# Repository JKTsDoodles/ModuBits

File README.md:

# ModuBits
This is a versatile set of prototyping boards and modules designed to fit chassis measuring 100mm wide and 120mm deep. Each module allows for easy integration of various connectors and components, enabling efficient prototyping and experimentation in electronics projects. 

ECAD tool: KiCad 9.99 (nightly)

MCAD tool: FreeCAD 1.0.2

Compatible chassis:
- [K93-10436-H7-L120](https://jlcmc.com/product/b/U01/BR9212/aluminum-box-(jlc)---104*36*120mm,-split,-monolithic)
- [K97-10473-H7-L120](https://jlcmc.com/product/b/U01/BR9241/aluminum-box-(jlc)---104*73*120mm,-split,-monolithic)
- [K96-10463-H7-L120](https://jlcmc.com/product/b/U01/BR9259/aluminum-box-(jlc)---104*63*120mm,-split,-monolithic)
- [K127-13031-H7-L120](https://jlcmc.com/product/b/U01/BR10337/aluminum-box-(jlc)---130*31*120mm,-monolithic,-with-handles)

BNC module:

Note that BNC connector parts of this type may share the same footprint but differ in the height of the connector in order to vendor lock their customers. Check for the height of your part, which is 6.25mm in this example.

BNC reference design:
  
Chassis K127-13031-H7-L120:
  
Chassis K93-10436-H7-L120:
  
Chassis K97-10473-H7-L120:
  
Chassis K96-10463-H7-L120:

Barrel Jack module (PJ-063AH):

Barrel jack reference design:
  
Chassis K127-13031-H7-L120:
  
Chassis K93-10436-H7-L120:
  
Chassis K97-10473-H7-L120:
  
Chassis K96-10463-H7-L120:

3.5mm Audio Jack module (SJ3-35083D-TR):

Audio jack reference design:

Chassis K127-13031-H7-L120:
  
Chassis K93-10436-H7-L120:
  
Chassis K97-10473-H7-L120:
  
Chassis K96-10463-H7-L120:

4mm Banana Jack module (Banana_Cliff_FCR7350B_S16N-PC_Horizontal):

4mm Banana jack reference design:
  
Chassis K127-13031-H7-L120:
  
Chassis K93-10436-H7-L120:
  
Chassis K97-10473-H7-L120:
  
Chassis K96-10463-H7-L120:

Connectorless PMMA plastic optic fiber receiver (IF-D91B):

Connectorless PMMA plastic optic fiber receiver reference design:

Chassis K127-13031-H7-L120:
  
Chassis K93-10436-H7-L120:
  
Chassis K97-10473-H7-L120:
  
Chassis K96-10463-H7-L120:

Connectorless PMMA plastic optic fiber transmitter (IF-E96E):

Connectorless PMMA plastic optic fiber transmitter reference design:

Chassis K127-13031-H7-L120:
  
Chassis K93-10436-H7-L120:
  
Chassis K97-10473-H7-L120:
  
Chassis K96-10463-H7-L120:

Right-angle tactile switch (PTS645V):

Right-angle tactile switch reference design:

Chassis K127-13031-H7-L120:
  
Chassis K93-10436-H7-L120:
  
Chassis K97-10473-H7-L120:
  
Chassis K96-10463-H7-L120:

The indices of the modules used to determine the position of the modules on the protoboard:
<p align="center">

</p>

The white bars at the bottom edge of the protoboard mark the decadal numbers and the index has a range of 0..72.

The following table lists the reference coordinates for the frontpanel hole if the module is sitting on the reference point (index == 0). The coordinates of the respective frontpanel hole can be calculated by adding (if the protoboard is component side up) or subtracting (if the protoboard is component side down) 1.27mm times index (of the module), since the modules are on a 50mil(1.27mm) grid.

I may write a FreeCAD script at some point to automate the generation of the frontpanel MCAD files.

| Chassis                         | Cutout Coordinates [X/Y] mm 4mm Banana D=11.5mm | Cutout Coordinates [X/Y] mm BNC D=13mm | Cutout Coordinates [X/Y] mm IF-D91B D=6.3mm | Cutout Coordinates [X/Y] mm IF-E96E D=6.3mm | Cutout Coordinates [X/Y] mm PJ-063AH D=7mm | Cutout Coordinates [X/Y] mm PTS645V D=3.6mm | Cutout Coordinates [X/Y] mm SJ3-35083D-TR D=5.2mm |
|---------------------------------|-------------------------------------------------|----------------------------------------|---------------------------------------------|---------------------------------------------|--------------------------------------------|---------------------------------------------|---------------------------------------------------|
| K93-10436-H7-L120, level1, up   | 12.63+index*1.27 / 19.92                        | 15.18+index*1.27 / 20.72               | 11.36+index*1.27 / 20.6                     | 11.36+index*1.27 / 20.6                     | 12.63+index*1.27 / 18.62                   | 11.38+index*1.27 / 17.12                    | 10.09+index*1.27 / 16.15                          |
| K127-13031-H7-L120, level1, up  | 13.03+index*1.27 / 18.33                        | 15.55+index*1.27 / 19.14               | 11.76+index*1.27 / 19.02                    | 11.76+index*1.27 / 19.02                    | 13.03+index*1.27 / 17.02                   | 11.79+index*1.27 / 15.53                    | 10.49+index*1.27 / 14.56                          |
| K97-10473-H7-L120, level1, up   | 12.63+index*1.27 / 19.92                        | 15.17+index*1.27 / 20.70               | 11.36+index*1.27 / 20.64                    | 11.36+index*1.27 / 20.64                    | 12.63+index*1.27 / 18.62                   | 11.38+index*1.27 / 17.12                    | 10.09+index*1.27 / 16.15                          |
| K97-10473-H7-L120, level4, down | 91.37-index*1.27 / 53.06                        | 88.83-index*1.27 / 52.25               | 92.64-index*1.27 / 52.41                    | 92.64-index*1.27 / 52.41                    | 91.37-index*1.27 / 54.36                   | 92.62-index*1.27 / 55.86                    | 93.91-index*1.27 / 56.83                          |
| K96-10463-H7-L120, level1, up   | 12.63+index*1.27 / 19.93                        | 15.17+index*1.27 / 20.74               | 11.36+index*1.27 / 20.58                    | 11.36+index*1.27 / 20.58                    | 12.63+index*1.27 / 18.63                   | 11.38+index*1.27 / 17.14                    | 10.09+index*1.27 / 16.16                          |
| K96-10463-H7-L120, level4, down | 91.37-index*1.27 / 43.07                        | 88.83-index*1.27 / 42.26               | 92.64-index*1.27 / 42.35                    | 92.64-index*1.27 / 42.35                    | 91.37-index*1.27 / 44.38                   | 92.62-index*1.27 / 45.88                    | 93.91-index*1.27 / 46.84                          |

Following frontpanel was generated by opening "K93-10436-H7-L120_frontpanel_blank.FCStd" and plopping the python script "config_panel_K93-10436.py" into the Python console of FreeCAD. This script is hard-coded and ugly, yes, I'm acutely aware but it's also easy to read / understand and I'm not a coder. :3

The following image depicts the user area of the generator script that configures the frontpanel modifications.

I don't like my connectors getting mangled or smushed, so I designed a simple sacrificial part that will absorb the brunt of the impact force when the chassis is dropped or inadequately packaged. The part is attached to the chassis by using the M3 threads in the chassis, sandwiching the front panel between the chassis and the bumper part. I wanted to round the corners a bit further but I couldn't get the "fillet" tool to do its thing since the FreeCAD implementation is less forgiving than the equivalent tool in commercial MCAD tools.

The Tarantinorino is a corner piece with rubbery feet on all relevant sides to allow these chassis to either be used stacked like a tower or standing on the desk as an instrument centipede.

Same as above but with the improved DockLink-Frame:

This DockLink-Base-plate allows to secure stacks of chassis with a DockLink-Frame to any surface that can be screwed into with M6 bolts, like optical breadboards (M6, grid: 25mm):

Here's a short video showing off the DockLink-Base-plate with two attached chassis:
[DockLink-Base-plate](https://drive.proton.me/urls/AMNBBSNWWW#FV0qRknL7xtg)

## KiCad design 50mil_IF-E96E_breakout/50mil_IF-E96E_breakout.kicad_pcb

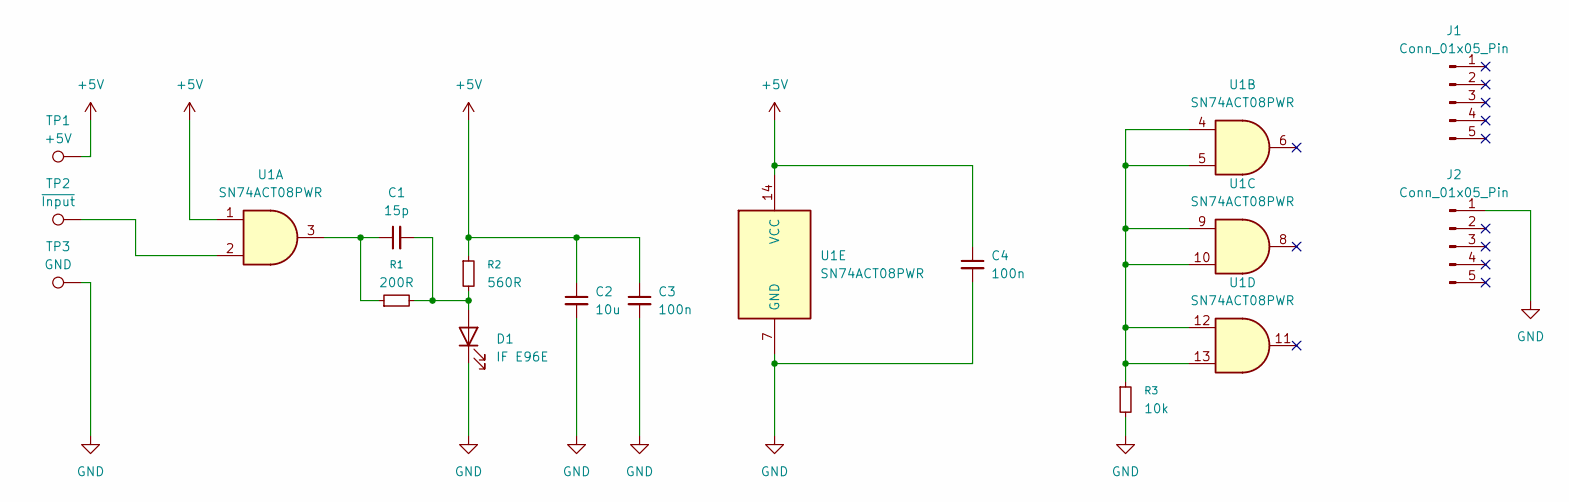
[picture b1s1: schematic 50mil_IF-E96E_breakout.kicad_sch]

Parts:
C1: 15p; C_0805_2012Metric_Pad1.18x1.45mm_HandSolder
C2: 10u; C_0805_2012Metric_Pad1.18x1.45mm_HandSolder
C3, C4: 100n; C_0805_2012Metric_Pad1.18x1.45mm_HandSolder
D1: IF E96E; IF-E96E
J1, J2: Conn_01x05_Pin; PinHeader_1x05_P1.27mm_Vertical
R1: 200R; R_0805_2012Metric_Pad1.20x1.40mm_HandSolder
R2: 560R; R_0805_2012Metric_Pad1.20x1.40mm_HandSolder
R3: 10k; R_0805_2012Metric_Pad1.20x1.40mm_HandSolder
TP1: +5V; TestPoint_THTPad_2.0x2.0mm_Drill1.0mm
TP2: ~{Input}; TestPoint_THTPad_2.0x2.0mm_Drill1.0mm
TP3: GND; TestPoint_THTPad_2.0x2.0mm_Drill1.0mm
U1: SN74ACT08PWR; TSSOP-14_4.4x5mm_P0.65mm

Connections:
+5V: C2.1, C3.1, C4.1, R2.1, TP1.1, U1.1, U1.14 (VCC)
GND: C2.2, C3.2, C4.2, D1.1 (K), J2.1, R3.2, TP3.1, U1.7 (GND)
unnamed: C1.1, R1.1, U1.3
unnamed: C1.2, D1.2 (A), R1.2, R2.2
unnamed: R3.1, U1.4, U1.5, U1.9, U1.10, U1.12, U1.13
unnamed: TP2.1, U1.2

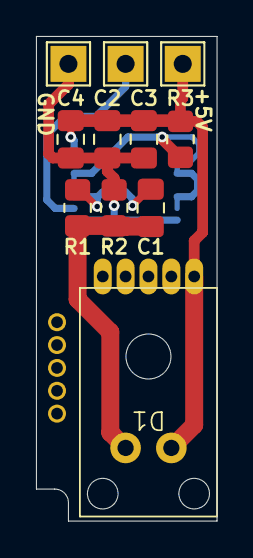
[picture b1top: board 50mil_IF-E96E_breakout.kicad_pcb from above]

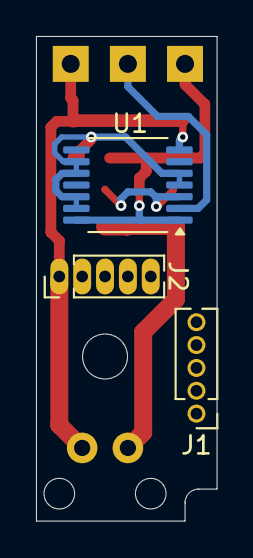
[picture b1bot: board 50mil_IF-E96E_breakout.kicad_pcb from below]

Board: 2 copper layers, 10.0 x 26.9 mm, 14 parts (3 on the bottom side), 6 nets.

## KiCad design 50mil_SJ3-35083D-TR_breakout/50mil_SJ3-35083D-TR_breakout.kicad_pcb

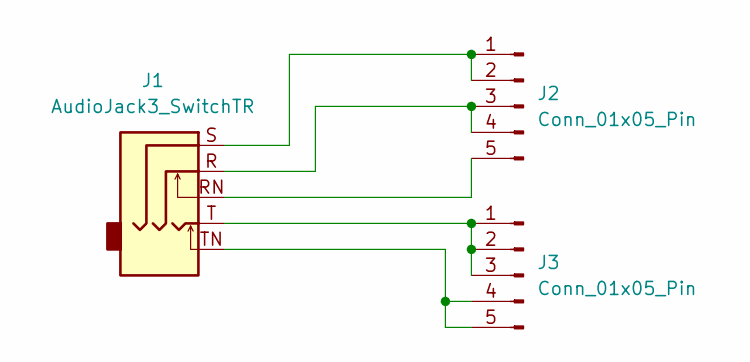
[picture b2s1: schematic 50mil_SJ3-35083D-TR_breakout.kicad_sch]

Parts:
J1: AudioJack3_SwitchTR; SJ3-35083D-TR
J2, J3: Conn_01x05_Pin; PinHeader_1x05_P1.27mm_Vertical

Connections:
unnamed: J1.S, J2.1, J2.2
unnamed: J1.R, J2.3, J2.4
unnamed: J1.RN, J2.5
unnamed: J1.T, J3.1, J3.2, J3.3
unnamed: J1.TN, J3.4, J3.5

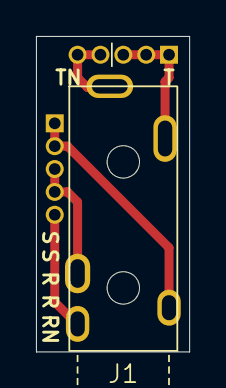
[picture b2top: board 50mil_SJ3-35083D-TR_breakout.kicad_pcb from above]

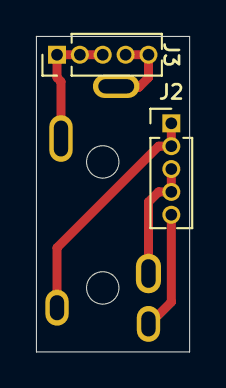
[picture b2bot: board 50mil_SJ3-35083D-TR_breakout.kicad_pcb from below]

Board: 2 copper layers, 8.5 x 17.5 mm, 3 parts (2 on the bottom side), 5 nets.

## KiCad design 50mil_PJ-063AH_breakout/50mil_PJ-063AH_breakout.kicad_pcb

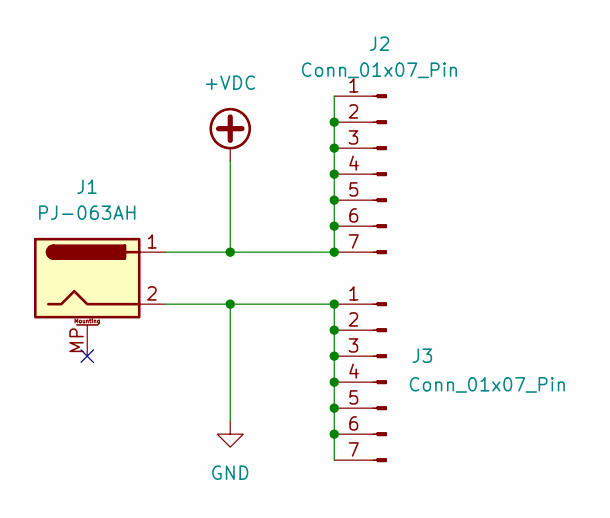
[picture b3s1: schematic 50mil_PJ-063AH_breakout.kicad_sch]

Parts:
J1: PJ-063AH; BarrelJack_CUI_PJ-063AH_Horizontal
J2, J3: Conn_01x07_Pin; PinHeader_1x07_P1.27mm_Vertical

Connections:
+VDC: J1.1, J2.1, J2.2, J2.3, J2.4, J2.5, J2.6, J2.7
GND: J1.2, J3.1, J3.2, J3.3, J3.4, J3.5, J3.6, J3.7

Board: 2 copper layers, 3 parts (2 on the bottom side), 2 nets, no tracks yet.

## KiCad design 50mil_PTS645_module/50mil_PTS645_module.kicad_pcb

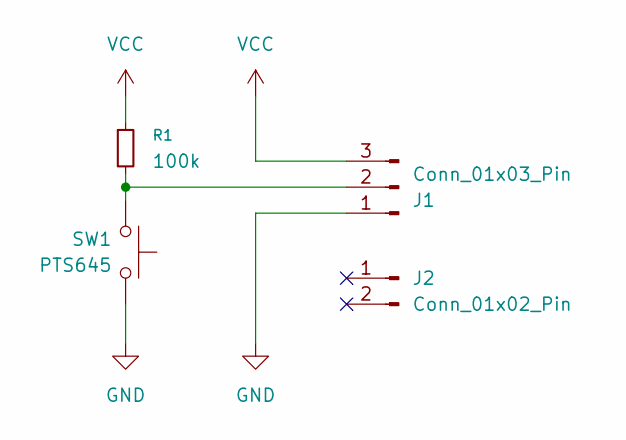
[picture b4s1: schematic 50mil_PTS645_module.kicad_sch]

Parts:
J1: Conn_01x03_Pin; PinHeader_1x03_P1.27mm_Vertical
J2: Conn_01x02_Pin; PinHeader_1x02_P1.27mm_Vertical
R1: 100k; R_0805_2012Metric_Pad1.20x1.40mm_HandSolder
SW1: PTS645; SW_Tactile_SPST_Angled_PTS645Vx58-2LFS

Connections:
GND: J1.1, SW1.1
unnamed: J1.2, R1.2, SW1.2
VCC: J1.3, R1.1

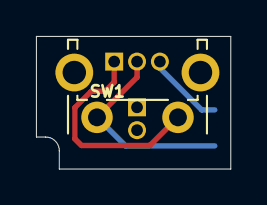
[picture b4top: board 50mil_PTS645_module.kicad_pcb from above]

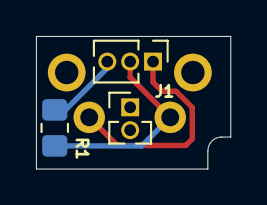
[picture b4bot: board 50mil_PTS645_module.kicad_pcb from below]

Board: 2 copper layers, 10.8 x 7.4 mm, 4 parts (3 on the bottom side), 3 nets.

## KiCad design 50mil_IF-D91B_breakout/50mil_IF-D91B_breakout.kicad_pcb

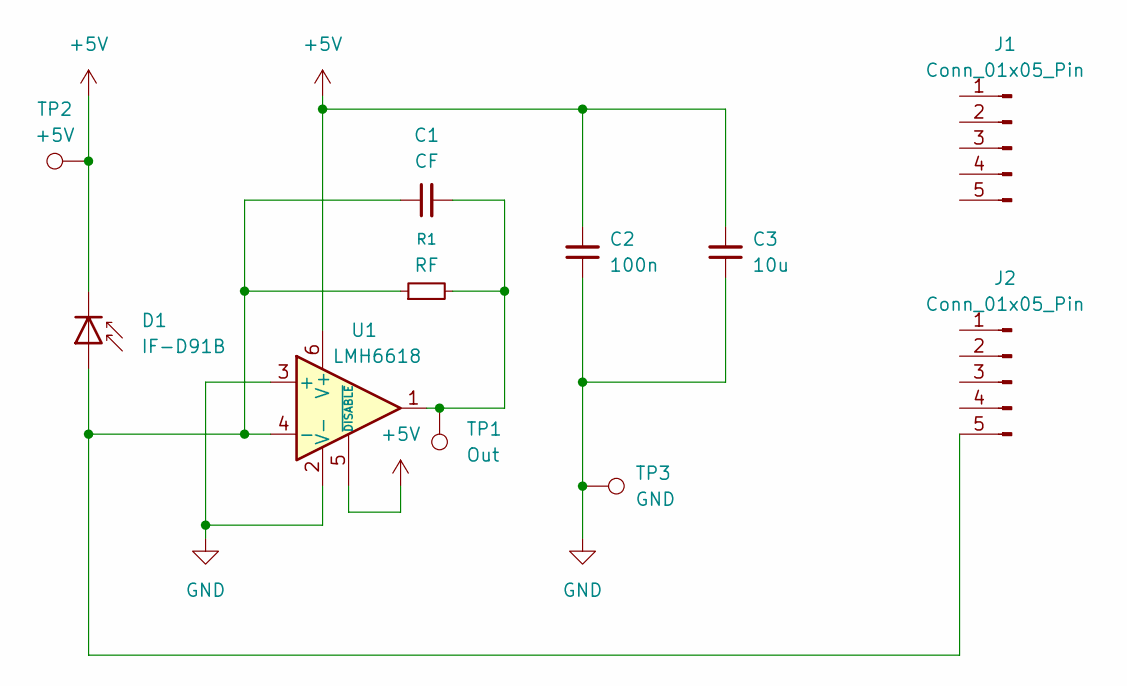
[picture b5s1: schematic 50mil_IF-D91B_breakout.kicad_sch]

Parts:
C1: CF; C_0805_2012Metric_Pad1.18x1.45mm_HandSolder
C2: 100n; C_0805_2012Metric_Pad1.18x1.45mm_HandSolder
C3: 10u; C_0805_2012Metric_Pad1.18x1.45mm_HandSolder
D1: IF-D91B
J1, J2: Conn_01x05_Pin; PinHeader_1x05_P1.27mm_Vertical
R1: RF; R_0805_2012Metric_Pad1.20x1.40mm_HandSolder
TP1: Out; TestPoint_THTPad_2.0x2.0mm_Drill1.0mm
TP2: +5V; TestPoint_THTPad_2.0x2.0mm_Drill1.0mm
TP3: GND; TestPoint_THTPad_2.0x2.0mm_Drill1.0mm
U1: LMH6618; TSOT-23-6_HandSoldering

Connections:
+5V: C2.2, C3.2, D1.1 (K), TP2.1, U1.5 (~DISABLE), U1.6 (V+)
GND: C2.1, C3.1, TP3.1, U1.2 (V-), U1.3 (+)
unnamed: C1.2, R1.2, TP1.1, U1.1
unnamed: C1.1, D1.2 (A), J2.5, R1.1, U1.4 (-)

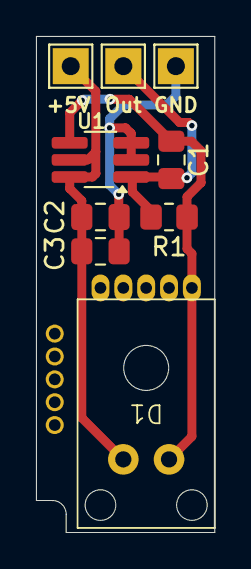
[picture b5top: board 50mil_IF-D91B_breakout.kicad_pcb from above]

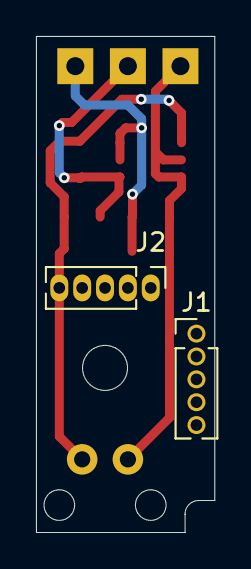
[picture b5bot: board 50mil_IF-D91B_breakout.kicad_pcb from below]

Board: 2 copper layers, 9.9 x 27.6 mm, 11 parts (2 on the bottom side), 4 nets.

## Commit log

2025-09-14 add pictures to repo
2025-09-14 added first pics to the readme
2025-09-14 fixed broken links
2025-09-14 add more pictures
2025-09-14 added more images with descriptions
2025-09-14 removed some artifact
2025-09-17 added first bunch of KiCad files
2025-09-17 added dummy footprints for the tactile switch breakout and the 4mm banana jack breakout
2025-10-07 added missing dummy footprints, added examples to the protoboard
2025-10-07 added MCAD files and images for the K127-13031-H7-L120 chassis
2025-10-07 added images of the K127... chassis to the README.md
2025-10-07 added MCAD files for PTS645V
2025-10-07 added image file for PTS645V
2025-10-07 added image of the PTS645V to the README.md
2025-10-09 Update README.md, added version of used CAD tools
2025-10-09 Delete MCAD/K127-13031-H7-L120_reference_PTS645V.20251007-174026.FCBak
    deleted backup file
2025-10-10 added MCAD files and images for the chassis K93-10436-H7-L120
2025-10-10 added images for the chassis K93-10436-H7-L120
2025-10-10 added images of the reference designs related to the K93 chassis to the README.md
2025-10-11 updated images of the reference designs
2025-10-11 added files for chassis K97-10743-H7-L120
2025-10-11 added images related to chassis K97-10473-H7-L120 to the README.md
2025-10-11 added images for the reference boards
2025-10-11 Update README.md, added images of the Reference designs
2025-10-11 added image
2025-10-11 Update README.md, fixed some booboos
2025-10-12 added files / designs for chassis K96-10463-H7-L120
2025-10-12 Update README.md, added images for the chassis K96-10463-H7-L120
2025-10-12 added image of all current modules
2025-10-12 Update README.md, changed title image
2025-10-13 added index images of all current modules
2025-10-13 added images of the indeces of the modules README.md
2025-10-13 added protoboard detail image
2025-10-13 added the indices-image of the protoboard to the README.md
2025-10-13 Adding reference coordinates table to the README.md
2025-10-16 Updated the cutout coordinates table in the README.md
2025-10-19 added frontpanel generator script for chassis K93-10436 and an example with all 7 modules
2025-10-19 added generated frontpanel for chassis K93... to the README.md
2025-10-19 added picture of code snippet for the readme
2025-10-21 added the design files and image of a bumper for the K93-10436 chassis
2025-10-21 added some text/pics for the bumperino in the README.md
2025-10-21 added bumperinos to the K93... chassis
2025-10-21 added the bumperino to the example assembly and added the related text/images to the README.md
2025-10-27 added first revision of a still untested, stackable corner-piece for the K93-10436 chassis
2025-10-28 modified the tolerances for K93-10436-H7-L120_Tarantinorino_left.FCStd
2025-10-31 modified the tolerances for K93-10436-H7-L120_Tarantinorino_left and added recesses for tiny feet
2025-10-31 added parts and pictures for K93-10436-H7-L120 chassis centipede
2025-10-31 added pictures of the instrument centipede to the README.md
2025-11-01 modified the interlocking geometry for the K93-10436-H7-L120_Tarantinorino_left
2025-11-04 added design files for the DockLink-Frame (K93...chassis)
2025-11-04 Fixed a tolerance issue due to a distance inversion in one of the sketches. FreeCAD's solver fu**ed me, again. Without my consent.
2025-11-05 widened the inner dimension of the frame by two 1/10th of a mm for a looser fit, even on slightly undersized prints
2025-11-05 added DockLinkFrame-assembly for the K93-10436 chassis with ModuBits-demo-frontpanel
2025-11-05 Added a picture of the DockLink-Frame-Assembly to the README.md
2025-11-08 added chamfers to the DockLinkFrame parts and added the mirrored version
2025-11-09 added design files for a DockLink-Base-plate for securing DockLink-Frames to optical breadboards
2025-11-09 changed the design for the DockLink-Base-plate
2025-11-09 Added "DockLink-Base-plate" to the README.md
2025-11-10 Added a video(link) showing off the DockLink-Base-plate to the README.md
2025-11-15 added design files for the first draft of the DockLink-Frame for the K97... chassis
